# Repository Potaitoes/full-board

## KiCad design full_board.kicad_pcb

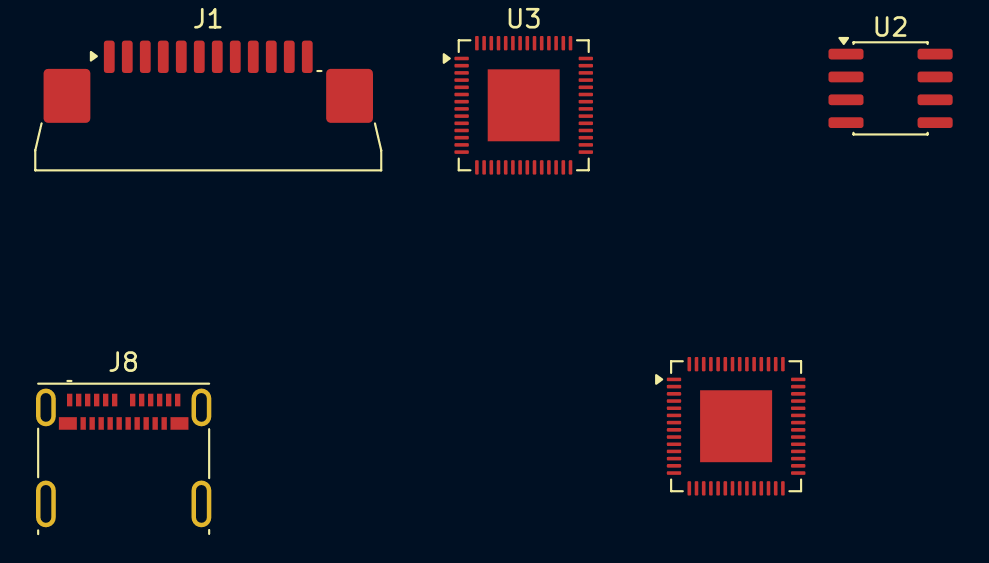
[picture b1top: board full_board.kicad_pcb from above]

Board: 2 copper layers, 5 parts (0 on the bottom side), 6 nets, no tracks yet.

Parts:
J1: Conn_01x12_Pin; JUSHUO_AFA07-S12FCA-00_1x12-1MP_P1.0mm_Horizontal
J8: USB_C_Receptacle; USB_C_Receptacle_Molex_105450-0101
U1, U3: ESP32-S3; QFN-56-1EP_7x7mm_P0.4mm_EP4x4mm
U2: TJA1051T; SOIC-8_3.9x4.9mm_P1.27mm

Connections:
unnamed: J8.A1 (GND), J8.A12 (GND), J8.B1 (GND), J8.B12 (GND)
unnamed: J8.A4 (VBUS), J8.A9 (VBUS), J8.B4 (VBUS), J8.B9 (VBUS)
unnamed: U1.2 (VDD3P3), U1.3 (VDD3P3)
unnamed: U1.55 (VDDA), U1.56 (VDDA)
unnamed: U3.2 (VDD3P3), U3.3 (VDD3P3)
unnamed: U3.55 (VDDA), U3.56 (VDDA)

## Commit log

2026-03-16 making progress on the ethernet circuit
2026-03-16 EOD commit
